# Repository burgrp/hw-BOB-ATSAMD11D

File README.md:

# hw-BOB-ATSAMD11D
ATSAMD11D breakout board

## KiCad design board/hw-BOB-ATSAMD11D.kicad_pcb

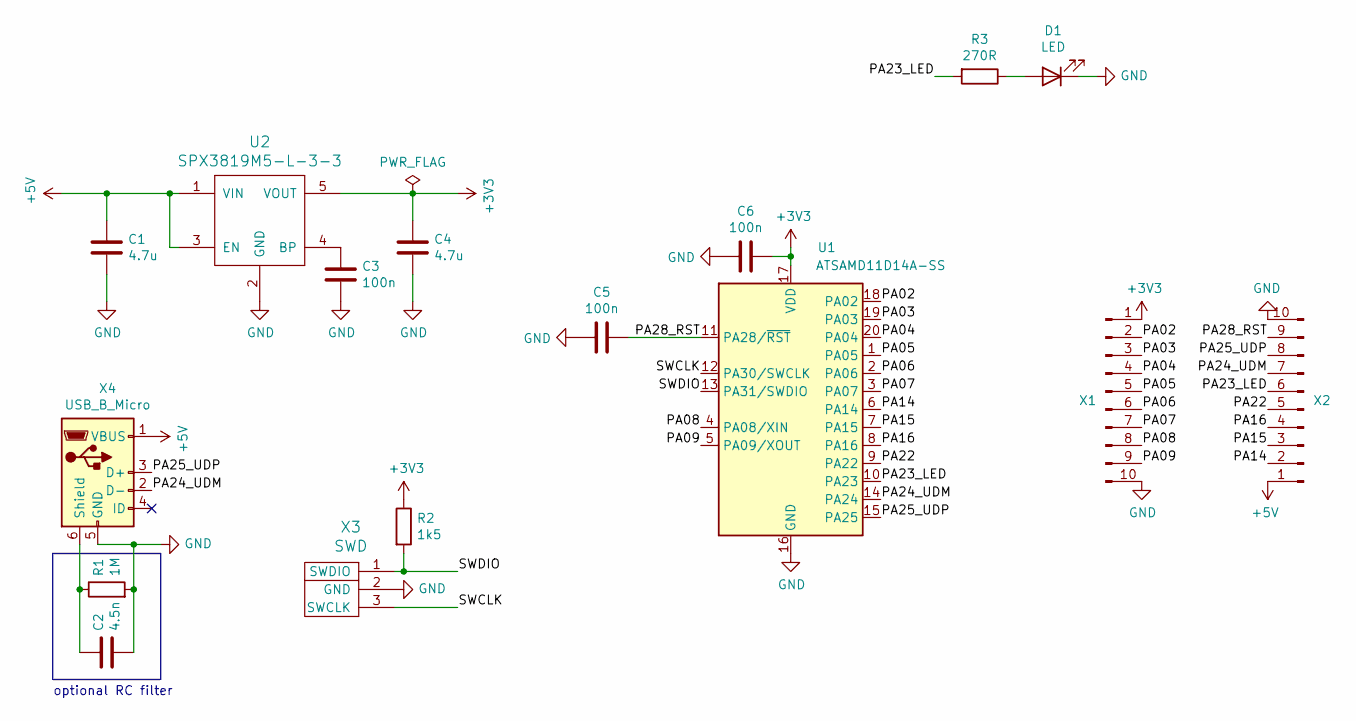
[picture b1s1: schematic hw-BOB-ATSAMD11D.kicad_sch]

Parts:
C1, C4: 4.7u; C_0805_2012Metric_Pad1.18x1.45mm_HandSolder
C2: 4.5n; C_0805_2012Metric_Pad1.18x1.45mm_HandSolder
C3, C5, C6: 100n; C_0805_2012Metric_Pad1.18x1.45mm_HandSolder
D1: LED; LED_0805_2012Metric_Pad1.15x1.40mm_HandSolder
R1: 1M; R_0805_2012Metric_Pad1.20x1.40mm_HandSolder
R2: 1k5; R_0805_2012Metric_Pad1.20x1.40mm_HandSolder
R3: 270R; R_0805_2012Metric_Pad1.20x1.40mm_HandSolder
U1: ATSAMD11D14A-SS; SOIC-20W_7.5x12.8mm_P1.27mm
U2: SPX3819M5-L-3-3; SOT-23-5_HandSoldering
X1, X2: Conn_01x10_Male; PinHeader_1x10_P2.54mm_Vertical
X3: SWD
X4: USB_B_Micro; conn_usb_B_micro_smd-2

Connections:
+3V3: C4.2, C6.1, R2.1, U1.17 (VDD), U2.5 (VOUT), X1.1
+5V: C1.2, U2.1 (VIN), U2.3 (EN), X2.1, X4.1 (VBUS)
/PA02: U1.18 (PA02), X1.2
/PA03: U1.19 (PA03), X1.3
/PA04: U1.20 (PA04), X1.4
/PA05: U1.1 (PA05), X1.5
/PA06: U1.2 (PA06), X1.6
/PA07: U1.3 (PA07), X1.7
/PA08: U1.4 (PA08/XIN), X1.8
/PA09: U1.5 (PA09/XOUT), X1.9
/PA14: U1.6 (PA14), X2.2
/PA15: U1.7 (PA15), X2.3
/PA16: U1.8 (PA16), X2.4
/PA22: U1.9 (PA22), X2.5
/PA23_LED: R3.2, U1.10 (PA23), X2.6
/PA24_UDM: U1.14 (PA24), X2.7, X4.2 (D-)
/PA25_UDP: U1.15 (PA25), X2.8, X4.3 (D+)
/PA28_RST: C5.1, U1.11 (PA28/~RST), X2.9
/SWCLK: U1.12 (PA30/SWCLK), X3.3 (SWCLK)
/SWDIO: R2.2, U1.13 (PA31/SWDIO), X3.1 (SWDIO)
GND: C1.1, C2.2, C3.1, C4.1, C5.2, C6.2, D1.1 (K), R1.2, U1.16 (GND), U2.2 (GND), X1.10, X2.10, X3.2 (GND), X4.5 (GND)
unnamed: D1.2 (A), R3.1
unnamed: C3.2, U2.4 (BP)
unnamed: C2.1, R1.1, X4.6 (Shield)

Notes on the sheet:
optional RC filter

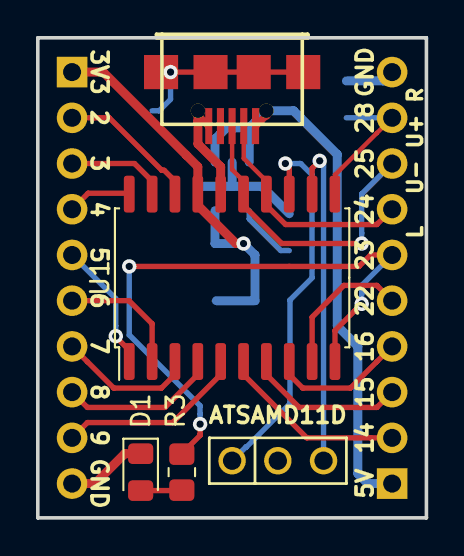
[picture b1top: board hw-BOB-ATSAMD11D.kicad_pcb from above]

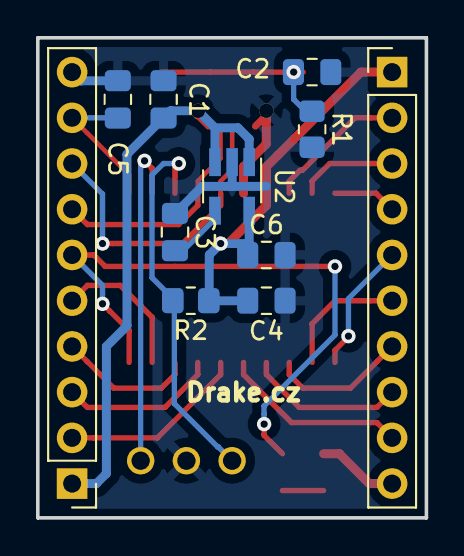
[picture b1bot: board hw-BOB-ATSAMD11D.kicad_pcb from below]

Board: 2 copper layers, 21.6 x 26.7 mm, 16 parts (11 on the bottom side), 24 nets.
